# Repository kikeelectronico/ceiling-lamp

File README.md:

View this project on [CADLAB.io](https://cadlab.io/project/24088). 

# Celling lamp

An AC output controlled by an ESP8266 and powered by AC main

### Firmwares

#### Test

This firmware allows you to test the hardware if needed. It will change the relay status each 400 millisenconds when the button is pressed and it will send the push button status via serial communication.

#### AdafruitIO

This firmware is based in the Adafruit example for comumnicate with its MQTT broker called AdafruitIO. You can see more in <a href="https://io.adafruit.com">io.adafruit.com</a>

In order to use it you should set:

- Your WiFi setting
- You Adafruit user name
- API Key from Adafruit IO
- The MQTT feed which will be used in Adafruit IO

#### MQTT

This firmware allows you to communicate with a MQTT broker. For example, you can install your own MQTT broker in a Raspberry Pi.

This is the actual firmware that I am using at home with this circuit, and it is prepared for being working 24/7. It does:

- Recovery after a power failure.
- Wake up message
- Reconnect message
- Serial debug
- WiFi reconnect if the signal is lost
- MQTT Broker reconnect if the signal is lost

### For future revisions

- `Diode Footprint`: It is wrong in the PCB design
- `ESP8266`: ESP8266 as SoC instead of the ESP8266-12E module
- `UPS`: Uninterrupted Power System. Cesar Fernández idea
- `Capacitive button`: A capacitive external button that acts as the push button

***

<br /><span xmlns:dct="http://purl.org/dc/terms/" property="dct:title">Ceiling lamp</span> by <span xmlns:cc="http://creativecommons.org/ns#" property="cc:attributionName">Enrique Gómez</span> licensed by <a rel="license" href="http://creativecommons.org/licenses/by-sa/4.0/">Creative Commons Attribution-ShareAlike 4.0 International License</a>.<br /><br />

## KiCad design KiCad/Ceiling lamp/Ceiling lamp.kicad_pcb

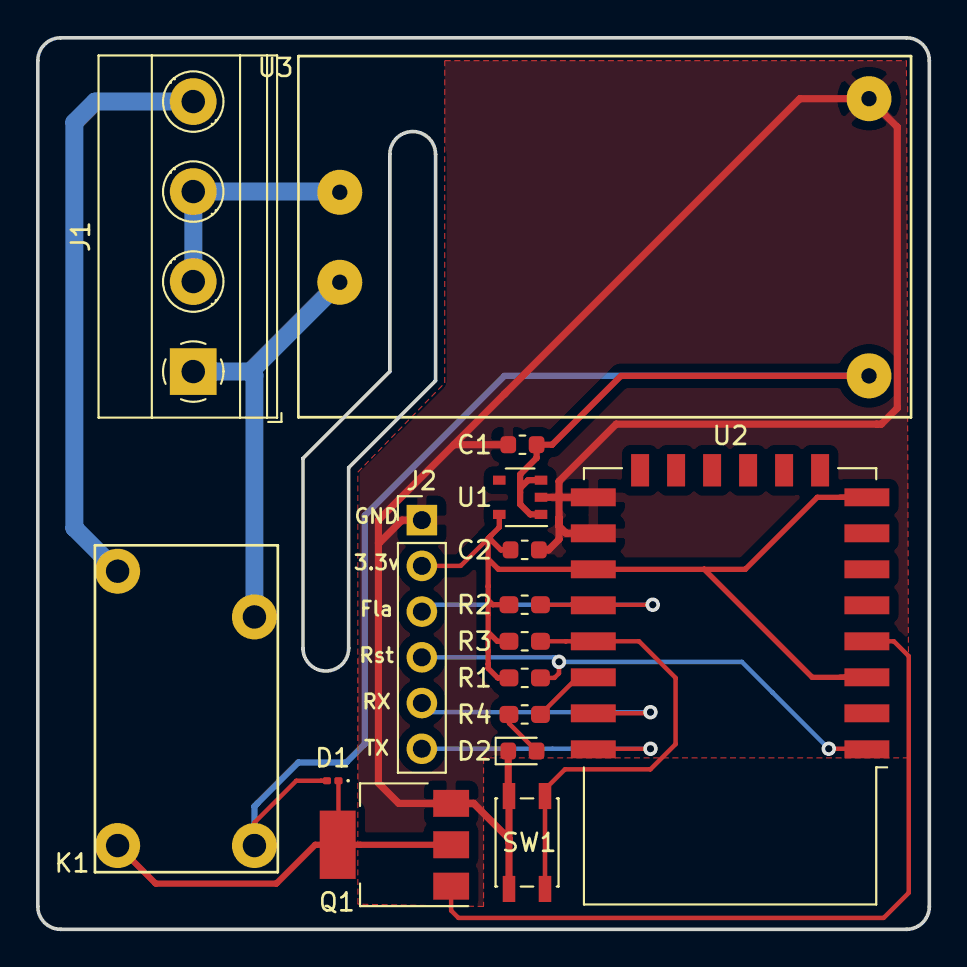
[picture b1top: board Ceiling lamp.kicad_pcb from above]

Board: 2 copper layers, 49.5 x 49.5 mm, 16 parts (0 on the bottom side), 15 nets.

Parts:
C1, C2: 0.47uF; C_0603_1608Metric
D1: RGF1B; D_0201_0603Metric
D2: LED_verde; LED_0603_1608Metric
J1: Screw_Terminal_01x04; TerminalBlock_Phoenix_MKDS-1,5-4_1x04_P5.00mm_Horizontal
J2: Conn_01x06_Female; PinHeader_1x06_P2.54mm_Vertical
K1: 1461492-2; Rele-1461492-2
Q1: FDN537N; SOT-223
R1, R2, R3: 10k; R_0603_1608Metric_Pad1.05x0.95mm_HandSolder
R4: 82.5; R_0603_1608Metric_Pad1.05x0.95mm_HandSolder
SW1: SW_Push; SW_SPST_EVQP2
U1: BU33SD5WG-TR; TSOP-5_1.65x3.05mm_P0.95mm
U2: ESP-12E
U3: HLK-PM01

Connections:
+3V3: C2.1, J2.2, R1.2, R2.1, R3.2, U1.5, U2.3, U2.8, U2.17
+5V: C1.1, D1.2, K1.1, U1.1, U1.3, U3.4
/Button: R3.1, SW1.1, U2.19
/Flash: J2.3, R2.2, U2.18
/LED: R4.2, U2.20
/RX: J2.5, U2.21
/Relay: Q1.1, U2.4
/RelayC: J1.4, K1.3
/RelayL: J1.1, K1.4, U3.2
/Rst: J2.4, R1.1, U2.1
/TX: J2.6, U2.22
GND: C1.2, C2.2, D2.1, J2.1, Q1.3, SW1.2, U1.2, U2.15, U2.16, U3.3
unnamed: D1.1, K1.2, Q1.2, Q1.4
unnamed: D2.2, R4.1
unnamed: J1.2, J1.3, U3.1

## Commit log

2021-03-26 kick off
2021-03-26 readme
2021-03-26 license
2021-03-26 Backlink to CADLAB.io has been added.
2021-03-27 pcb changes v3
2021-03-27 docs
2021-03-27 gerbers
2021-03-27 readme update
2021-06-27 3D case
2021-06-27 3D case cover

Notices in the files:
KiCad/Ceiling lamp/Ceiling lamp.kicad_pcb:
CC BY-SA 4.0
